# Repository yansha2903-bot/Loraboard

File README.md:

# LoraBoard
A custom ESP32-S3 LoRa development board designed for long-range wireless communication projects.

## Overview
LoraBoard is a custom PCB designed around the ESP32-S3 microcontroller and the SX1262 LoRa transceiver. The board is intended for low-power, long-range communication applications such as mesh networking, remote monitoring, IoT devices, and sensor networks.

The project was designed using KiCad and includes a complete schematic, PCB layout, and manufacturing files.

## Features
- ESP32-S3 microcontroller
- SX1262 LoRa transceiver
- USB connectivity for programming and power
- Compact PCB design
- Long-range wireless communication
- Suitable for Meshtastic and IoT applications
- Hardware
- Main Components
- ESP32-S3
- SX1262 LoRa Radio
- USB Interface
- Antenna Connector
- Repository Structure

## Images

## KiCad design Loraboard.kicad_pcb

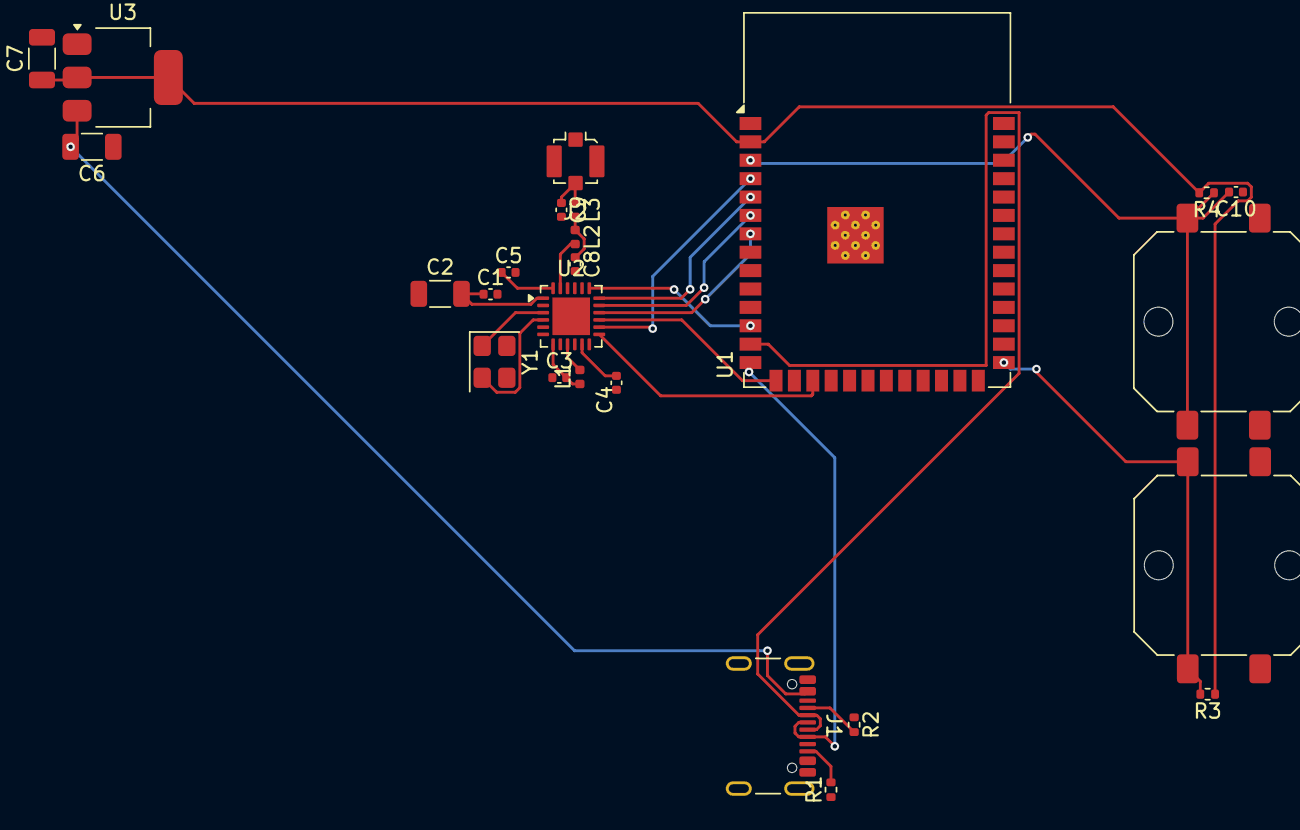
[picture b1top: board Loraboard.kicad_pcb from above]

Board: 2 copper layers, 25 parts (0 on the bottom side), 26 nets.

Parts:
C1, C3, C4, C5, C10: 100nF; C_0402_1005Metric
C2, C6, C7: 10µF; C_1206_3216Metric
C8: 2.7pF; C_0402_1005Metric
C9: 3.3pF; C_0402_1005Metric
J1: USB_C_Receptacle_USB2.0_14P; USB_C_Receptacle_GCT_USB4105-xx-A_16P_TopMnt_Horizontal
J2: Conn_Coaxial; U.FL_Molex_MCRF_73412-0110_Vertical
L1: 15µH; L_0402_1005Metric
L2: 3.9nH; L_0402_1005Metric
L3: 12nH; L_0402_1005Metric
R1, R2: 5.1k; R_0402_1005Metric
R3, R4: 10kΩ; R_0402_1005Metric
SW1, SW2: SW_Push; SW_Push_1P1T_NO_CK_PTS125Sx85PSMTR
U1: ESP32-S3-WROOM-1
U2: SX1262IMLTRT; QFN-24-1EP_4x4mm_P0.5mm_EP2.6x2.6mm
U3: AMS1117-3.3; SOT-223-3_TabPin2
Y1: 32 MHz; Crystal_SMD_3225-4Pin_3.2x2.5mm

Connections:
+3V3: C7.1, R3.1, R4.2, U1.2 (3V3), U3.2 (VO)
+5V: C6.2, J1.A4 (VBUS), J1.A9 (VBUS), J1.B4 (VBUS), J1.B9 (VBUS), U3.3 (VI)
/BUSY: U1.4 (IO4), U2.14 (BUSY)
/DIO1: U1.17 (IO9), U2.13 (DIO1)
/MISO: U1.7 (IO7), U2.16 (MISO)
/MOSI: U1.6 (IO6), U2.17 (MOSI)
/NSS: U1.12 (IO8), U2.19 (NSS)
/RESET: U1.15 (IO3), U2.15 (~RESET)
/SCK: U1.5 (IO5), U2.18 (SCK)
/USB_D+: J1.A6 (D+), J1.B6 (D+), U1.14 (USB_D+)
/USB_D-: J1.A7 (D-), J1.B7 (D-), U1.13 (USB_D-)
GND: C1.2, C2.1, C3.1, C4.1, C5.2, C6.1, C7.2, C8.2, C9.2, C10.1, J1.A1 (GND), J1.A12 (GND), J1.B1 (GND), J1.B12 (GND), J2.2 (Ext), R1.1, R2.1, SW1.1, SW2.1, U1.1 (GND), U1.40 (GND), U1.41 (GND), U2.2 (GND), U2.5 (GND), U2.8 (GND), U2.20 (GND), U2.25 (GND), U3.1 (GND)
unnamed: C8.1, L2.1, L3.2
unnamed: J1.A5 (CC1), R2.2
unnamed: J1.B5 (CC2), R1.2
unnamed: C9.1, J2.1 (In), L3.1
unnamed: C10.2, R4.1, SW2.2, U1.3 (EN)
unnamed: R3.2, SW1.2, U1.27 (IO0)
unnamed: L1.2, U2.9 (DCC_SW)
unnamed: L2.2, U2.23 (RFO)
unnamed: C4.2, U2.11 (VBAT_IO)
unnamed: C1.1, C2.2, U2.1 (VDD_IN)
unnamed: C3.2, L1.1, U2.7 (VREG)
unnamed: C5.1, U2.24 (VR_PA)
unnamed: U2.3 (XTA), Y1.1
unnamed: U2.4 (XTB), Y1.2

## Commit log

2026-06-18 Create LICENSE
